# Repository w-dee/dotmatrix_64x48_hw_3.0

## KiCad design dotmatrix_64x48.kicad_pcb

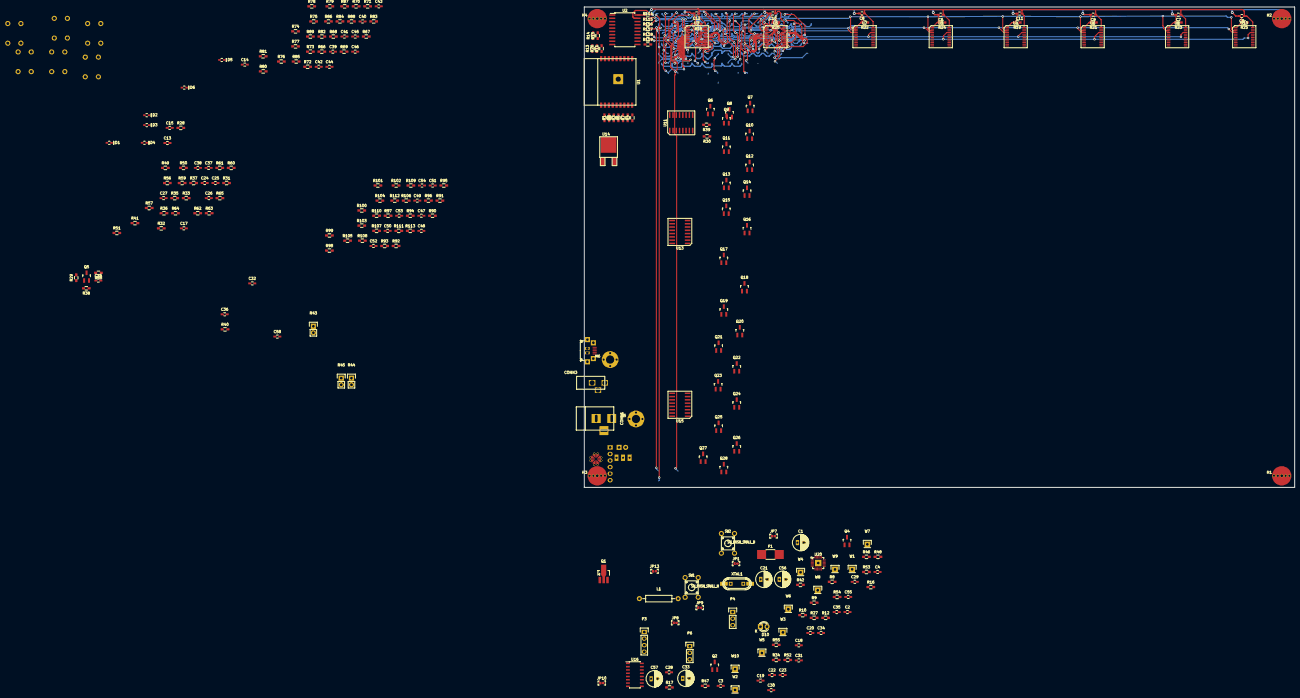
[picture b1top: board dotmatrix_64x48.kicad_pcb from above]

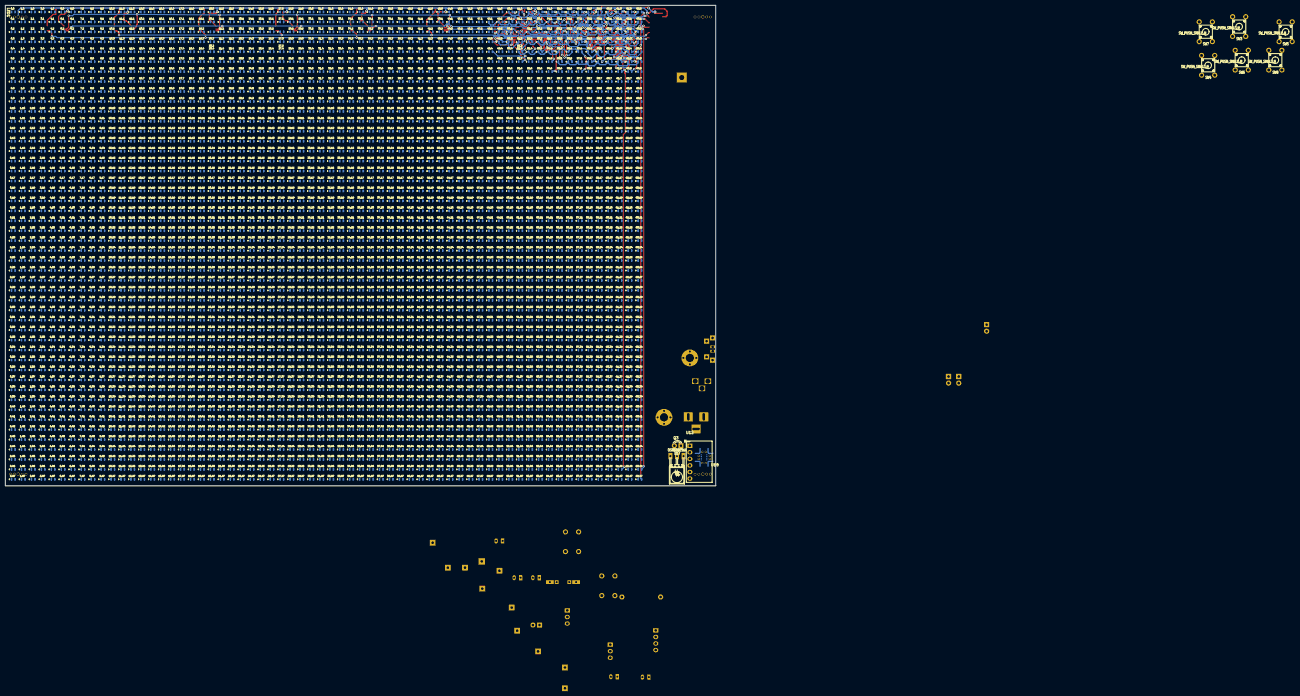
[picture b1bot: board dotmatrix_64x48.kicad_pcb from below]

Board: 2 copper layers, 275.0 x 186.0 mm, 271 parts (11 on the bottom side), 292 nets.

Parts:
C1, C21, C33, C56, C57: 100u; C_Radial_D6.3_L11.2_P2.5_hand_soldering
C2, C4, C5, C6, C7, C8, C9, C10, C11, C12, C13, C14, C15, C16, C17, C18, C19, C20, C22, C23, C24, C25, C26, C27, C28, C30, C32, C34, C35, C36, C37, C38, C39, C40, C41, C42, C43, C44, C45, C46, C47, C48, C49, C50, C51, C52, C53, C54, C55, C58: 1u; C_0603_HandSoldering
C3: 220p; C_0603_HandSoldering
C29, C31: 22p; C_0603_HandSoldering
CONN1: BARREL_JACK
CONN2: USB_OTG; ZX62R-B-5P
CONN3: BARREL_JACK; DC-JACK-3.5mm
D1, D2, D3, D4, D5, D6: D_Schottky_Small; SOD-523-mod
D10: Led_Small; LED-3MM
F1: FUSE; R_1812_HandSoldering
H1, H2, H3, H4: TEST_1P; MountingHole_stud-M3
H5, H6: TEST_1P; MountingHole_3.2mm_M3
JP1, JP7, JP8, JP9, JP10, JP13: Jumper_NC_Small; SolderJumper
L1: 2.2uH; Resistor_Horizontal_RM15mm
LED1: LED64x48; LED1608_Handsoldering_64x48
P3: CONN_01X04; Pin_Header_Straight_1x04
P4, P6: CONN_01X03; Pin_Header_Straight_1x03
Q1: Q_NPN_BCE RN5006; SOT89-3_Housing_Handsoldering
Q2, Q4: Q_NPN_BEC; SOT-23_Handsoldering
Q3: NJL7302L-F3; LED-3MM
Q5, Q6, Q7, Q8, Q9, Q10, Q11, Q12, Q13, Q14, Q15, Q16, Q17, Q18, Q19, Q20, Q21, Q22, Q23, Q24, Q25, Q26, Q27, Q28: AO3401; SOT-23_Handsoldering
R1, R2, R3, R4, R6, R7, R13, R14, R15, R17, R26, R46, R52, R114, R115, R116, R117, R118, R119: 120R; R_0603_HandSoldering
R5, R11, R18, R28, R34, R53, R54, R55: 10k; R_0603_HandSoldering
R8, R16, R27, R58, R59, R60, R61, R62, R63, R64, R65, R82, R83, R84, R85, R86, R87, R88, R89, R106, R107, R108, R109, R110, R111, R112, R113: 4.7k; R_0603_HandSoldering
R9, R10, R40: 22k; R_0603_HandSoldering
R12, R48: 1k; R_0603_HandSoldering
R19, R20, R21, R22, R23, R24, R25: R; R_0603_HandSoldering
R29, R30, R31, R32, R33, R35, R36, R37, R66, R67, R68, R69, R70, R71, R72, R73, R90, R91, R92, R93, R94, R95, R96, R97: 10R; R_0603_HandSoldering
R38, R39, R41, R49, R50, R51, R56, R57, R74, R75, R76, R77, R78, R79, R80, R81, R98, R99, R100, R101, R102, R103, R104, R105: 4.7k DNI; R_0603_HandSoldering
R42: 10k DNI; R_0603_HandSoldering
R43, R44, R45: 10k; Pin_Header_Straight_1x02
R47: 120R DNI; R_0603_HandSoldering
SW1, SW2, SW3, SW4, SW5, SW6, SW7, SW8: SW_PUSH_SMALL_H; TACT-SW-4P
U1: WROOM-02
U2: 74VHC541; SOIC-20W_7.5x12.8mm_Pitch1.27mm_W
U3, U4, U5, U6, U7, U8, U9, U10: LED1642GW; SOIC-24-0.65mm-w8.0mm
U11, U13, U15: 74HCT595; SOIC-16-1.27mm
U12: AE-BME280
U14: NJU7223; TO-252-2Lead
U16: CH340G; SOIC-16_3.9x9.9mm_Pitch1.27mm
U17: OSRB38C9AA; IRM2161_LAY
U18: BME280; BME280-handsoldering
U20: CP2104; QFN-24-1EP_4x4mm_Pitch0.5mm-handsoldering
W1, W2, W3, W4, W5, W6, W7, W8, W9, W10: TEST_1P; Pin_Header_Straight_1x01
XTAL1: 12MHz; Crystal_HC49-U_Vertical_SMD_Universal

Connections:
/row_driver/SEL1: D1.1, R90.2, U15.7
/row_driver/SEL2: D2.1, R91.2, U15.6
/row_driver/SEL3: D3.1, R92.2, U15.5
/row_driver/SEL4: D4.1, R93.2, U15.4
/row_driver/SEL5: D5.1, R94.2, U15.3
/row_driver/SEL6: D6.1, R95.2, U15.2
/row_driver/f_r0/IN0: R29.2, U11.7
/row_driver/f_r0/IN1: R30.2, U11.6
/row_driver/f_r0/IN2: R31.2, U11.5
/row_driver/f_r0/IN3: R32.2, U11.4
/row_driver/f_r0/IN4: R33.2, U11.3
/row_driver/f_r0/IN5: R35.2, U11.2
/row_driver/f_r0/IN6: R36.2, U11.1
/row_driver/f_r0/IN7: R37.2, U11.15
/row_driver/f_r8/IN0: R66.2, U13.7
/row_driver/f_r8/IN1: R67.2, U13.6
/row_driver/f_r8/IN2: R68.2, U13.5
/row_driver/f_r8/IN3: R69.2, U13.4
/row_driver/f_r8/IN4: R70.2, U13.3
/row_driver/f_r8/IN5: R71.2, U13.2
/row_driver/f_r8/IN6: R72.2, U13.1
/row_driver/f_r8/IN7: R73.2, U13.15
/row_driver/f_r16/IN6: R96.2, U15.1
/row_driver/f_r16/IN7: R97.2, U15.15
BUTTONSENSE: R13.2, R28.2, SW3.2, SW4.2, SW5.2, SW6.2, SW7.2, SW8.2, W9.1
COLCLK: R115.2, U3.3, U4.3, U5.3, U6.3, U7.3, U8.3, U9.3, U10.3, U11.11, U13.11, U15.11, W2.1
COLLATCH: R116.2, U3.4, U4.4, U5.4, U6.4, U7.4, U8.4, U9.4, U10.4, W3.1
COLPWCLK0: R117.2, U3.21, U4.21, U7.21, U8.21, W5.1
COLPWCLK1: R118.2, U5.21, U6.21, U9.21, U10.21, W10.1
COLSER: R114.2, U3.2, W1.1
COLSEROUT: U10.22, U15.14, W4.1
DC_IN: CONN1.1, F1.1, JP7.1
DTR: Q4.2, R54.2, U16.13, U20.23
ESPVDD: C18.1, C19.1, C20.1, C32.1, C33.1, C34.1, C35.1, C36.1, C55.1, C56.1, C57.1, JP8.1, L1.2, R5.2, R8.1, R9.1, R10.1, R11.2, R27.1, R40.1, R45.2, U1.1, U12.1, U17.3, U18.2, U18.6, U18.8
E_AIN: C58.1, Q3.2, R26.2, R43.1
E_COLCLK: R1.1, U2.3
E_COLLATCH: R2.1, U2.4
E_COLSER: R3.1, U2.2
E_HC595LATCH: R6.1, U2.9
E_PWCLK: R14.2, U2.6, U2.7
E_RXD: R14.1, R16.1, U1.11
E_SCL: R4.2, R9.2, R52.1, U1.8
E_SDA: R46.1, U1.14
E_TXD: R17.1, U1.12
GND: C1.2, C4.2, C5.2, C6.2, C7.2, C8.2, C9.2, C10.2, C11.2, C12.2, C13.2, C14.2, C15.2, C16.2, C17.2, C18.2, C19.2, C20.2, C21.2, C22.2, C23.2, C24.2, C25.2, C26.2, C27.2, C28.2, C29.2, C30.2, C31.2, C32.2, C33.2, C34.2, C35.2, C36.2, C37.2, C38.2, C39.2, C40.2, C41.2, C42.2, C43.2, C44.2, C45.2, C46.2, C47.2, C48.2, C49.2, C50.2, C51.2, C52.2, C53.2, C54.2, C55.2, C56.2, C57.2, C58.2, CONN1.2, CONN1.3, CONN2.5, CONN2.6, H1.1, H2.1, H3.1, H4.1, H5.1, H6.1, P3.2, P4.1, P6.1, P6.3, Q1.3, Q3.1, R18.2, R19.2, R20.2, R21.2, R22.2, R23.2, R24.2, R25.2, R34.2, R42.1, R47.1, R47.2, R48.1, R58.1, R59.1, R60.1, R61.1, R62.1, R63.1, R64.1, R65.1, R82.1, R83.1, R84.1, R85.1, R86.1, R87.1, R88.1, R89.1, R106.1, R107.1, R108.1, R109.1, R110.1, R111.1, R112.1, R113.1, SW1.2, SW2.2, U1.9, U1.13, U1.18, U2.1, U2.5, U2.8, U2.10, U2.19, U3.1, U4.1, U5.1, U6.1, U7.1, U8.1, U9.1, U10.1, U11.8, U11.13, U12.2, U13.8, U13.13, U14.3, U15.8, U15.13, U16.1, U17.2, U18.1, U18.5, U18.7, U20.2, U20.25
GPIO0_BTN: Q4.3, R4.1, SW1.1
HC595LATCH: R119.2, U11.12, U13.12, U15.12, W7.1
HC595RESET: U11.10, U13.10, U15.10, W6.1
HC595SEROUT: U11.9, W8.1
IR_IN: R15.2, R40.2, U17.1
IR_OUT: C2.2, D10.2, R7.1
LEDLOGICVDD: C5.1, C6.1, C7.1, C8.1, C9.1, C10.1, C11.1, C12.1, JP13.2, L1.1, P6.2, R28.1, U2.20, U3.24, U4.24, U5.24, U6.24, U7.24, U8.24, U9.24, U10.24
LEDVDD: C13.1, C14.1, C15.1, C16.1, C17.1, C24.1, C25.1, C26.1, C27.1, C37.1, C38.1, C39.1, C40.1, C41.1, C42.1, C43.1, C44.1, C45.1, C46.1, C47.1, C48.1, C49.1, C50.1, C51.1, C52.1, C53.1, C54.1, JP1.2, Q5.2, Q6.2, Q7.2, Q8.2, Q9.2, Q10.2, Q11.2, Q12.2, Q13.2, Q14.2, Q15.2, Q16.2, Q17.2, Q18.2, Q19.2, Q20.2, Q21.2, Q22.2, Q23.2, Q24.2, Q25.2, Q26.2, Q27.2, Q28.2, R38.1, R39.1, R41.1, R49.1, R50.1, R51.1, R56.1, R57.1, R74.1, R75.1, R76.1, R77.1, R78.1, R79.1, R80.1, R81.1, R98.1, R99.1, R100.1, R101.1, R102.1, R103.1, R104.1, R105.1, U11.16, U13.16, U15.16
unnamed: C1.1, C23.1, JP13.1, U14.1
unnamed: C2.1, C3.2, R12.1
unnamed: C3.1, Q1.1, R12.2, R42.2
unnamed: C28.1, C30.1, JP8.2, R53.1, U16.4, U16.16, U20.5, U20.6, U20.7
unnamed: C29.1, U16.7, XTAL1.1
unnamed: C31.1, U16.8, XTAL1.2
unnamed: CONN2.1, JP7.2
unnamed: CONN3.2, CONN3.3, Q1.2
unnamed: D1.2, SW3.1
unnamed: D2.2, SW4.1
unnamed: D3.2, SW5.1
unnamed: D4.2, SW6.1
unnamed: D5.2, SW7.1
unnamed: D6.2, SW8.1
unnamed: D10.1, R48.2
unnamed: JP9.1, U16.2, U20.21
unnamed: JP10.1, U16.3, U20.20
unnamed: Q2.1, R54.1
unnamed: Q4.1, R55.1
unnamed: Q5.1, R29.1, R38.2
unnamed: Q6.1, R30.1, R39.2
unnamed: Q7.1, R31.1, R41.2
unnamed: Q8.1, R32.1, R49.2
unnamed: Q9.1, R33.1, R50.2
unnamed: Q10.1, R35.1, R51.2
unnamed: Q11.1, R36.1, R56.2
unnamed: Q12.1, R37.1, R57.2
unnamed: Q13.1, R66.1, R74.2
unnamed: Q14.1, R67.1, R75.2
unnamed: Q15.1, R68.1, R76.2
unnamed: Q16.1, R69.1, R77.2
unnamed: Q17.1, R70.1, R78.2
unnamed: Q18.1, R71.1, R79.2
unnamed: Q19.1, R72.1, R80.2
unnamed: Q20.1, R73.1, R81.2
unnamed: Q21.1, R90.1, R98.2
unnamed: Q22.1, R91.1, R99.2
unnamed: Q23.1, R92.1, R100.2
unnamed: Q24.1, R93.1, R101.2
unnamed: Q25.1, R94.1, R102.2
unnamed: Q26.1, R95.1, R103.2
unnamed: Q27.1, R96.1, R104.2
unnamed: Q28.1, R97.1, R105.2
unnamed: R1.2, U1.3
unnamed: R2.2, U1.4
unnamed: R3.2, U1.5
unnamed: R5.1, U1.2
unnamed: R7.2, R10.2, U1.7
unnamed: R13.1, U1.17
unnamed: R15.1, U1.10
unnamed: R18.1, U3.23
unnamed: R19.1, U4.23
unnamed: R20.1, U5.23
unnamed: R21.1, U6.23
unnamed: R22.1, U7.23
unnamed: R23.1, U8.23
unnamed: R24.1, U9.23
unnamed: R25.1, U10.23
unnamed: R26.1, U1.16
unnamed: R6.2, R34.1, U1.6
unnamed: R43.2, R44.1
unnamed: R44.2, R45.1
unnamed: R53.2, U20.9
unnamed: R114.1, U2.18
unnamed: R115.1, U2.17
unnamed: R116.1, U2.16
unnamed: R117.1, U2.14
unnamed: R118.1, U2.13
unnamed: R119.1, U2.11
unnamed: U3.22, U5.2
unnamed: U4.2, U9.22
unnamed: U4.22, U6.2
unnamed: U5.22, U7.2
unnamed: U6.22, U8.2
unnamed: U7.22, U9.2
unnamed: U8.22, U10.2
unnamed: U11.14, U13.9
unnamed: U13.14, U15.9
RST: Q2.3, R11.1, SW2.1, U1.15
RTS: Q2.2, R55.2, U16.14, U20.19
RXD: JP9.2, P3.3, R16.2
SCL: P4.2, R8.2, R52.2, U12.6, U18.4
SDA: P4.3, R27.2, R46.2, U12.4, U18.3
TXD: JP10.2, P3.4, R17.2
USB_D_N: CONN2.2, U16.6, U20.4
USB_D_P: CONN2.3, U16.5, U20.3
VCC: C4.1, C21.1, C22.1, CONN3.1, F1.2, JP1.1, U14.2, U20.8
ce0: LED1.1, U10.20
ce1: LED1.2, U10.18
ce2: LED1.3, U10.16
ce3: LED1.4, U10.14
ce4: LED1.5, U10.12
ce5: LED1.6, U10.10
ce6: LED1.7, U10.8
ce7: LED1.8, U10.6
ce8: LED1.9, U8.20
ce9: LED1.10, U8.18
ce10: LED1.11, U8.16
ce11: LED1.12, U8.14
ce12: LED1.13, U8.12
ce13: LED1.14, U8.10
ce14: LED1.15, U8.8
ce15: LED1.16, U8.6
ce16: LED1.17, U6.20
ce17: LED1.18, U6.18
ce18: LED1.19, U6.16
ce19: LED1.20, U6.14
ce20: LED1.21, U6.12
ce21: LED1.22, U6.10
ce22: LED1.23, U6.8
ce23: LED1.24, U6.6
ce24: LED1.25, U4.20
ce25: LED1.26, U4.18
ce26: LED1.27, U4.16
ce27: LED1.28, U4.14
ce28: LED1.29, U4.12
ce29: LED1.30, U4.10
ce30: LED1.31, U4.8
ce31: LED1.32, U4.6
ce32: LED1.33, U9.20
ce33: LED1.34, U9.18
ce34: LED1.35, U9.16
ce35: LED1.36, U9.14
ce36: LED1.37, U9.12
ce37: LED1.38, U9.10
ce38: LED1.39, U9.8
ce39: LED1.40, U9.6
ce40: LED1.41, U7.20
ce41: LED1.42, U7.18
ce42: LED1.43, U7.16
ce43: LED1.44, U7.14
ce44: LED1.45, U7.12
ce45: LED1.46, U7.10
ce46: LED1.47, U7.8
ce47: LED1.48, U7.6
ce48: LED1.49, U5.20
ce49: LED1.50, U5.18
ce50: LED1.51, U5.16
ce51: LED1.52, U5.14
ce52: LED1.53, U5.12
ce53: LED1.54, U5.10
ce54: LED1.55, U5.8
ce55: LED1.56, U5.6
ce56: LED1.57, U3.20
ce57: LED1.58, U3.18
ce58: LED1.59, U3.16
ce59: LED1.60, U3.14
ce60: LED1.61, U3.12
ce61: LED1.62, U3.10
ce62: LED1.63, U3.8
ce63: LED1.64, U3.6
co0: LED1.65, U10.19
co1: LED1.66, U10.17
co2: LED1.67, U10.15
co3: LED1.68, U10.13
co4: LED1.69, U10.11
co5: LED1.70, U10.9
co6: LED1.71, U10.7
co7: LED1.72, U10.5
co8: LED1.73, U8.19
co9: LED1.74, U8.17
co10: LED1.75, U8.15
co11: LED1.76, U8.13
co12: LED1.77, U8.11
co13: LED1.78, U8.9
co14: LED1.79, U8.7
co15: LED1.80, U8.5
co16: LED1.81, U6.19
co17: LED1.82, U6.17
co18: LED1.83, U6.15
co19: LED1.84, U6.13
co20: LED1.85, U6.11
co21: LED1.86, U6.9
co22: LED1.87, U6.7
co23: LED1.88, U6.5
co24: LED1.89, U4.19
co25: LED1.90, U4.17
co26: LED1.91, U4.15
co27: LED1.92, U4.13
co28: LED1.93, U4.11
co29: LED1.94, U4.9
co30: LED1.95, U4.7
co31: LED1.96, U4.5
co32: LED1.97, U9.19
co33: LED1.98, U9.17
co34: LED1.99, U9.15
co35: LED1.100, U9.13
co36: LED1.101, U9.11
co37: LED1.102, U9.9
co38: LED1.103, U9.7
co39: LED1.104, U9.5
co40: LED1.105, U7.19
co41: LED1.106, U7.17
co42: LED1.107, U7.15
co43: LED1.108, U7.13
co44: LED1.109, U7.11
co45: LED1.110, U7.9
co46: LED1.111, U7.7
co47: LED1.112, U7.5
co48: LED1.113, U5.19
co49: LED1.114, U5.17
co50: LED1.115, U5.15
co51: LED1.116, U5.13
co52: LED1.117, U5.11
co53: LED1.118, U5.9
co54: LED1.119, U5.7
co55: LED1.120, U5.5
co56: LED1.121, U3.19
co57: LED1.122, U3.17
co58: LED1.123, U3.15
co59: LED1.124, U3.13
co60: LED1.125, U3.11
co61: LED1.126, U3.9
co62: LED1.127, U3.7
co63: LED1.128, U3.5
r0: LED1.201, Q5.3, R58.2
r1: LED1.202, Q6.3, R59.2
r2: LED1.203, Q7.3, R60.2
r3: LED1.204, Q8.3, R61.2
r4: LED1.205, Q9.3, R62.2
r5: LED1.206, Q10.3, R63.2
r6: LED1.207, Q11.3, R64.2
r7: LED1.208, Q12.3, R65.2
r8: LED1.209, Q13.3, R82.2
r9: LED1.210, Q14.3, R83.2
r10: LED1.211, Q15.3, R84.2
r11: LED1.212, Q16.3, R85.2
r12: LED1.213, Q17.3, R86.2
r13: LED1.214, Q18.3, R87.2
r14: LED1.215, Q19.3, R88.2
r15: LED1.216, Q20.3, R89.2
r16: LED1.217, Q21.3, R106.2
r17: LED1.218, Q22.3, R107.2
r18: LED1.219, Q23.3, R108.2
r19: LED1.220, Q24.3, R109.2
r20: LED1.221, Q25.3, R110.2
r21: LED1.222, Q26.3, R111.2
r22: LED1.223, Q27.3, R112.2
r23: LED1.224, Q28.3, R113.2

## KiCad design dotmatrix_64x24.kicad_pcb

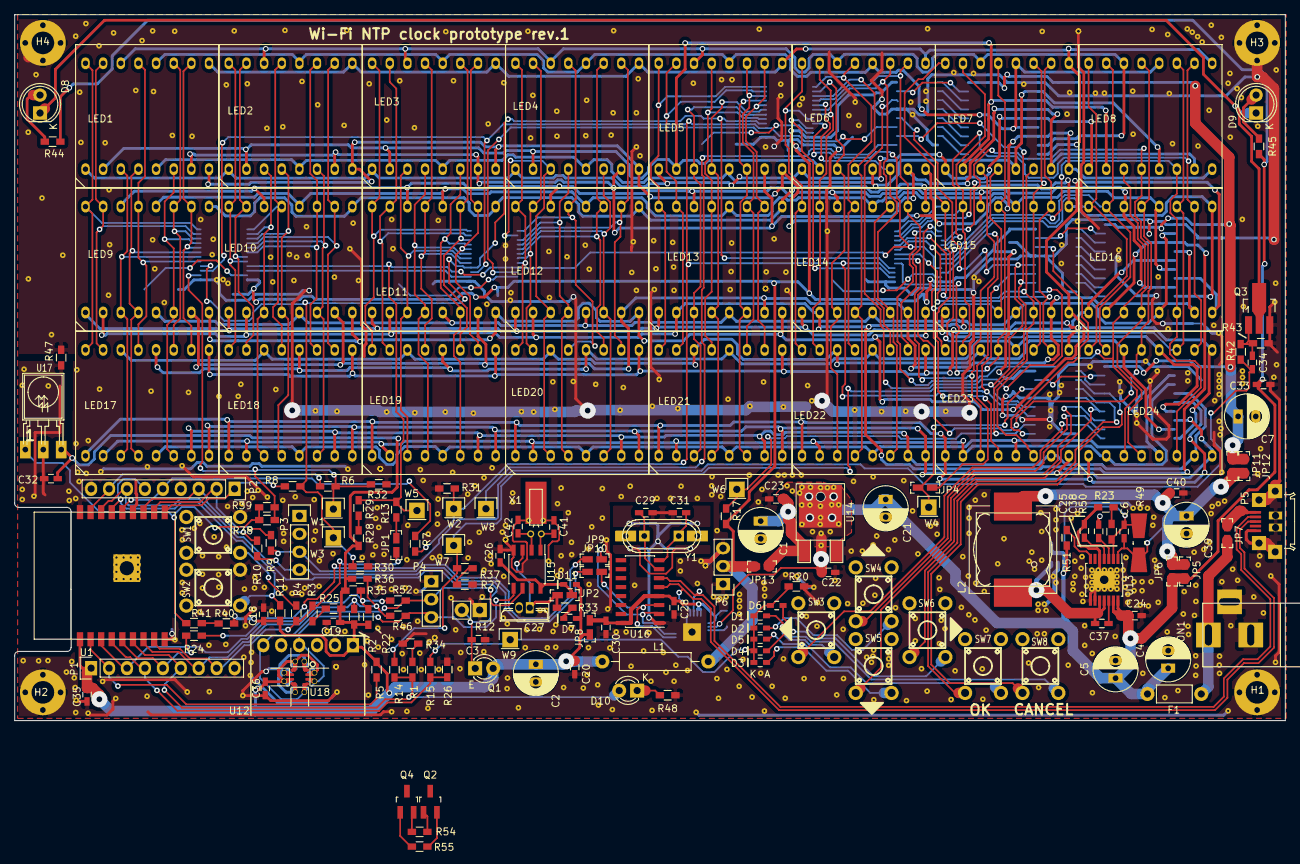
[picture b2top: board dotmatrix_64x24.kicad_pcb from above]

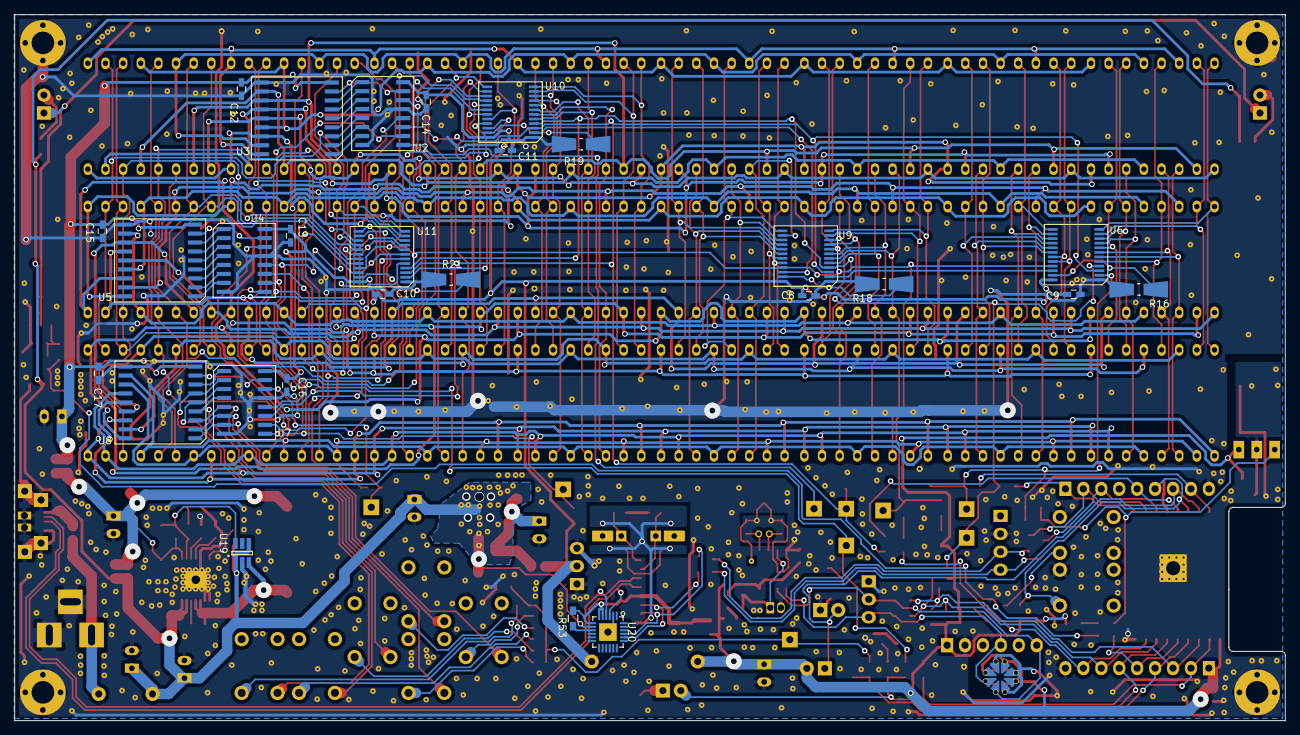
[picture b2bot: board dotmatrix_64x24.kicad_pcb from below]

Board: 2 copper layers, 180.0 x 100.0 mm, 201 parts (27 on the bottom side), 202 nets.

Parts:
C1, C2, C4, C5, C7, C21, C39: 100u; C_Radial_D6.3_L11.2_P2.5_hand_soldering
C3, C8, C9, C10, C11, C12, C13, C14, C15, C16, C17, C18, C19, C20, C22, C23, C24, C25, C26, C28, C30, C32, C33, C35, C36, C37, C38, C40: 1u; C_0603_HandSoldering
C6, C29, C31, C41, C42: 22p; C_0603_HandSoldering
C27: 0.22F; DCK_614
C34: 220p; C_0603_HandSoldering
CON1: BARREL_JACK
D1, D2, D3, D4, D5, D6, D7, D11: D_Schottky_Small; SOD-523-mod
D8, D9: Led_Small; LED-5MM
D10: Led_Small; LED-3MM
F1: FUSE; Resistor_Horizontal_RM7mm
H1, H2, H3, H4: TEST_1P; MountingHole_3.2mm_M3
JP1, JP2, JP4, JP5, JP6, JP7, JP8, JP9, JP10, JP11, JP12, JP13: Jumper_NC_Small; SolderJumper
L1: 100uH; Resistor_Horizontal_RM15mm
L2: 4.9uH; Choke_SMD_12x12mm_10.4x10.4mm_compat_h4.5mm_handsoldering
LED1, LED2, LED3, LED4, LED5, LED6, LED7, LED8, LED9, LED10, LED11, LED12, LED13, LED14, LED15, LED16, LED17, LED18, LED19, LED20, LED21, LED22, LED23, LED24: LED8x8; LED8x8,0.8x0.8inch
P1, P2: CONN_01X09; Pin_Header_Straight_1x09
P3: CONN_01X04; Pin_Header_Straight_1x04
P4, P6: CONN_01X03; Pin_Header_Straight_1x03
P5: USB_OTG; ZX62R-B-5P
Q1: NJL7302L-F3; LED-3MM
Q2, Q4: Q_NPN_BEC; SOT-23_Handsoldering
Q3: Q_NPN_BCE RN5006; SOT89-3_Housing_Handsoldering
R1, R2, R3, R5, R11, R17, R20, R22, R23, R25, R26, R27, R28, R29, R30, R31, R34, R35, R36, R37, R38, R39, R40, R41, R50, R51, R53, R54, R55: 10k; R_0603_HandSoldering
R4, R42, R48: 1k; R_0603_HandSoldering
R6, R7, R8, R9, R10, R13, R14, R15, R24, R33, R46, R52: 120R; R_0603_HandSoldering
R12: 50k; Pin_Header_Straight_1x02
R16, R18, R19, R21, R49: R; Resistor_SMDuniversal_0805to1206_HandSoldering
R32, R43: 10k DNI; R_0603_HandSoldering
R44, R45: 10R; R_0603_HandSoldering
R47: 120R DNI; R_0603_HandSoldering
SW1, SW2, SW3, SW4, SW5, SW6, SW7, SW8: SW_PUSH_SMALL_H; TACT-SW-4P
U1: WROOM-02
U2, U4, U7: 74HC595-alt-vdd; SOIC-16-1.27mm-w7.8mm
U3, U5, U8: TD62783; SOIC-18-1.27mm-w11.9mm
U6, U9, U10, U11: LED1642GW; SOIC-24-0.65mm-w8.0mm
U12: AE-BME280
U13: TPS54426; TSSOP-14-EP-hole_4.4x5mm_Pitch0.65mm
U14: NJU7223; TO-252-2Lead
U15: DS1307; SOIC-8_3.9x4.9mm_Pitch1.27mm
U16: CH340G; SOIC-16_3.9x9.9mm_Pitch1.27mm
U17: OSRB38C9AA; IRM2161_LAY
U18: BME280; BME280-handsoldering
U19: AP3419; SOT-23-6_Handsoldering
U20: CP2104; QFN-24-1EP_4x4mm_Pitch0.5mm-handsoldering
W1, W2, W3, W4, W5, W6, W7, W8, W9: TEST_1P; Pin_Header_Straight_1x01
X1: CRYSTAL_SMD; Crystal_Round_Horizontal_2mm_SHIELD
Y1: 12MHz; Crystal_HC49-U_Vertical_SMD_Universal

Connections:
/DC_IN: CON1.1, F1.1, JP7.1
/DTR: Q4.2, R54.2, U16.13, U20.23
/ESPVDD: C2.1, C18.1, C19.1, C20.1, C32.1, C35.1, C36.1, D7.2, D11.2, JP8.1, L1.2, P1.1, Q1.2, R2.1, R5.1, R11.1, R22.1, R25.1, R28.1, R35.1, R36.1, R40.1, U1.1, U12.1, U17.3, U18.2, U18.6, U18.8
/GPIO0_BTN: Q4.3, R4.1, SW1.1
/IR_IN: R38.1, R39.1, R41.2, U17.1
/IR_OUT: C34.2, R24.1, R42.1
/IR_Sensor_RTC/IR_LED_DRIVE: D8.1, D9.1, Q3.2
/LEDLOGICVDD: C8.1, C9.1, C10.1, C11.1, C13.1, C14.1, C16.1, JP13.2, L1.1, P6.2, R17.1, U2.16, U4.16, U6.24, U7.16, U9.24, U10.24, U11.24
/RST: P2.6, Q2.3, R11.2, SW2.1, U1.15
/RTS: Q2.2, R55.2, U16.14, U20.19
/RXD: JP9.2, P3.3, R9.2
/SCL: P4.2, R52.2, U12.6, U15.6, U18.4
/SDA: P4.3, R46.2, U12.4, U15.5, U18.3
/Sheet57A04605/BUTTONSENSE: D1.1, D2.1, D3.1, D4.1, D5.1, D6.1, R15.2, R20.1, W9.1
/Sheet57A04605/COLCLK: R7.2, R31.1, U2.11, U4.11, U6.3, U7.11, U9.3, U10.3, U11.3, W2.1
/Sheet57A04605/COLLATCH: R8.2, R30.1, U6.4, U9.4, U10.4, U11.4, W3.1
/Sheet57A04605/COLPWCLK: R13.2, R29.2, U6.21, U9.21, U10.21, U11.21, W5.1
/Sheet57A04605/COLSER: R6.2, R32.1, R38.2, R39.2, U6.2, W1.1
/Sheet57A04605/COLSEROUT: JP4.2, U11.22
/Sheet57A04605/HC595LATCH: R14.2, R37.1, U2.12, U4.12, U7.12, W7.1
/Sheet57A04605/HC595RESET: R17.2, U2.10, U4.10, U7.10, W6.1
/Sheet57A04605/HC595SER: JP4.1, U7.14, W4.1
/Sheet57A04605/HC595SEROUT: U2.9, W8.1
/Sheet57A04605/LEDREG_FB: C6.2, R49.2, R50.1, U13.2, U19.6
/Sheet57A04605/LEDREG_LX: C37.1, L2.1, U13.10, U13.11, U19.3
/Sheet57A04605/LEDVDD: C7.1, C12.1, C15.1, C17.1, JP11.2, JP12.2, U3.9, U5.9, U8.9
/Sheet57A04605/SEL1: SW3.1, U7.7, U8.1
/Sheet57A04605/SEL2: SW4.1, U7.6, U8.2
/Sheet57A04605/SEL3: SW5.1, U7.5, U8.3
/Sheet57A04605/SEL4: SW6.1, U7.4, U8.4
/Sheet57A04605/SEL5: SW7.1, U7.3, U8.5
/Sheet57A04605/SEL6: SW8.1, U7.2, U8.6
/Sheet57A04605/c1: LED1.13, LED9.13, LED17.13, U6.5
/Sheet57A04605/c2: LED1.3, LED9.3, LED17.3, U6.6
/Sheet57A04605/c3: LED1.4, LED9.4, LED17.4, U6.7
/Sheet57A04605/c4: LED1.10, LED9.10, LED17.10, U6.8
/Sheet57A04605/c5: LED1.6, LED9.6, LED17.6, U6.9
/Sheet57A04605/c6: LED1.11, LED9.11, LED17.11, U6.10
/Sheet57A04605/c7: LED1.15, LED9.15, LED17.15, U6.11
/Sheet57A04605/c8: LED1.16, LED9.16, LED17.16, U6.12
/Sheet57A04605/c9: LED2.13, LED10.13, LED18.13, U6.13
/Sheet57A04605/c10: LED2.3, LED10.3, LED18.3, U6.14
/Sheet57A04605/c11: LED2.4, LED10.4, LED18.4, U6.15
/Sheet57A04605/c12: LED2.10, LED10.10, LED18.10, U6.16
/Sheet57A04605/c13: LED2.6, LED10.6, LED18.6, U6.17
/Sheet57A04605/c14: LED2.11, LED10.11, LED18.11, U6.18
/Sheet57A04605/c15: LED2.15, LED10.15, LED18.15, U6.19
/Sheet57A04605/c16: LED2.16, LED10.16, LED18.16, U6.20
/Sheet57A04605/c17: LED3.13, LED11.13, LED19.13, U9.5
/Sheet57A04605/c18: LED3.3, LED11.3, LED19.3, U9.6
/Sheet57A04605/c19: LED3.4, LED11.4, LED19.4, U9.7
/Sheet57A04605/c20: LED3.10, LED11.10, LED19.10, U9.8
/Sheet57A04605/c21: LED3.6, LED11.6, LED19.6, U9.9
/Sheet57A04605/c22: LED3.11, LED11.11, LED19.11, U9.10
/Sheet57A04605/c23: LED3.15, LED11.15, LED19.15, U9.11
/Sheet57A04605/c24: LED3.16, LED11.16, LED19.16, U9.12
/Sheet57A04605/c25: LED4.13, LED12.13, LED20.13, U9.13
/Sheet57A04605/c26: LED4.3, LED12.3, LED20.3, U9.14
/Sheet57A04605/c27: LED4.4, LED12.4, LED20.4, U9.15
/Sheet57A04605/c28: LED4.10, LED12.10, LED20.10, U9.16
/Sheet57A04605/c29: LED4.6, LED12.6, LED20.6, U9.17
/Sheet57A04605/c30: LED4.11, LED12.11, LED20.11, U9.18
/Sheet57A04605/c31: LED4.15, LED12.15, LED20.15, U9.19
/Sheet57A04605/c32: LED4.16, LED12.16, LED20.16, U9.20
/Sheet57A04605/c33: LED5.13, LED13.13, LED21.13, U10.5
/Sheet57A04605/c34: LED5.3, LED13.3, LED21.3, U10.6
/Sheet57A04605/c35: LED5.4, LED13.4, LED21.4, U10.7
/Sheet57A04605/c36: LED5.10, LED13.10, LED21.10, U10.8
/Sheet57A04605/c37: LED5.6, LED13.6, LED21.6, U10.9
/Sheet57A04605/c38: LED5.11, LED13.11, LED21.11, U10.10
/Sheet57A04605/c39: LED5.15, LED13.15, LED21.15, U10.11
/Sheet57A04605/c40: LED5.16, LED13.16, LED21.16, U10.12
/Sheet57A04605/c41: LED6.13, LED14.13, LED22.13, U10.13
/Sheet57A04605/c42: LED6.3, LED14.3, LED22.3, U10.14
/Sheet57A04605/c43: LED6.4, LED14.4, LED22.4, U10.15
/Sheet57A04605/c44: LED6.10, LED14.10, LED22.10, U10.16
/Sheet57A04605/c45: LED6.6, LED14.6, LED22.6, U10.17
/Sheet57A04605/c46: LED6.11, LED14.11, LED22.11, U10.18
/Sheet57A04605/c47: LED6.15, LED14.15, LED22.15, U10.19
/Sheet57A04605/c48: LED6.16, LED14.16, LED22.16, U10.20
/Sheet57A04605/c49: LED7.13, LED15.13, LED23.13, U11.5
/Sheet57A04605/c50: LED7.3, LED15.3, LED23.3, U11.6
/Sheet57A04605/c51: LED7.4, LED15.4, LED23.4, U11.7
/Sheet57A04605/c52: LED7.10, LED15.10, LED23.10, U11.8
/Sheet57A04605/c53: LED7.6, LED15.6, LED23.6, U11.9
/Sheet57A04605/c54: LED7.11, LED15.11, LED23.11, U11.10
/Sheet57A04605/c55: LED7.15, LED15.15, LED23.15, U11.11
/Sheet57A04605/c56: LED7.16, LED15.16, LED23.16, U11.12
/Sheet57A04605/c57: LED8.13, LED16.13, LED24.13, U11.13
/Sheet57A04605/c58: LED8.3, LED16.3, LED24.3, U11.14
/Sheet57A04605/c59: LED8.4, LED16.4, LED24.4, U11.15
/Sheet57A04605/c60: LED8.10, LED16.10, LED24.10, U11.16
/Sheet57A04605/c61: LED8.6, LED16.6, LED24.6, U11.17
/Sheet57A04605/c62: LED8.11, LED16.11, LED24.11, U11.18
/Sheet57A04605/c63: LED8.15, LED16.15, LED24.15, U11.19
/Sheet57A04605/c64: LED8.16, LED16.16, LED24.16, U11.20
/Sheet57A04605/r1: LED1.9, LED2.9, LED3.9, LED4.9, LED5.9, LED6.9, LED7.9, LED8.9, U3.18
/Sheet57A04605/r2: LED1.14, LED2.14, LED3.14, LED4.14, LED5.14, LED6.14, LED7.14, LED8.14, U3.17
/Sheet57A04605/r3: LED1.8, LED2.8, LED3.8, LED4.8, LED5.8, LED6.8, LED7.8, LED8.8, U3.16
/Sheet57A04605/r4: LED1.12, LED2.12, LED3.12, LED4.12, LED5.12, LED6.12, LED7.12, LED8.12, U3.15
/Sheet57A04605/r5: LED1.1, LED2.1, LED3.1, LED4.1, LED5.1, LED6.1, LED7.1, LED8.1, U3.14
/Sheet57A04605/r6: LED1.7, LED2.7, LED3.7, LED4.7, LED5.7, LED6.7, LED7.7, LED8.7, U3.13
/Sheet57A04605/r7: LED1.2, LED2.2, LED3.2, LED4.2, LED5.2, LED6.2, LED7.2, LED8.2, U3.12
/Sheet57A04605/r8: LED1.5, LED2.5, LED3.5, LED4.5, LED5.5, LED6.5, LED7.5, LED8.5, U3.11
/Sheet57A04605/r9: LED9.9, LED10.9, LED11.9, LED12.9, LED13.9, LED14.9, LED15.9, LED16.9, U5.18
/Sheet57A04605/r10: LED9.14, LED10.14, LED11.14, LED12.14, LED13.14, LED14.14, LED15.14, LED16.14, U5.17
/Sheet57A04605/r11: LED9.8, LED10.8, LED11.8, LED12.8, LED13.8, LED14.8, LED15.8, LED16.8, U5.16
/Sheet57A04605/r12: LED9.12, LED10.12, LED11.12, LED12.12, LED13.12, LED14.12, LED15.12, LED16.12, U5.15
/Sheet57A04605/r13: LED9.1, LED10.1, LED11.1, LED12.1, LED13.1, LED14.1, LED15.1, LED16.1, U5.14
/Sheet57A04605/r14: LED9.7, LED10.7, LED11.7, LED12.7, LED13.7, LED14.7, LED15.7, LED16.7, U5.13
/Sheet57A04605/r15: LED9.2, LED10.2, LED11.2, LED12.2, LED13.2, LED14.2, LED15.2, LED16.2, U5.12
/Sheet57A04605/r16: LED9.5, LED10.5, LED11.5, LED12.5, LED13.5, LED14.5, LED15.5, LED16.5, U5.11
/Sheet57A04605/r17: LED17.9, LED18.9, LED19.9, LED20.9, LED21.9, LED22.9, LED23.9, LED24.9, U8.18
/Sheet57A04605/r18: LED17.14, LED18.14, LED19.14, LED20.14, LED21.14, LED22.14, LED23.14, LED24.14, U8.17
/Sheet57A04605/r19: LED17.8, LED18.8, LED19.8, LED20.8, LED21.8, LED22.8, LED23.8, LED24.8, U8.16
/Sheet57A04605/r20: LED17.12, LED18.12, LED19.12, LED20.12, LED21.12, LED22.12, LED23.12, LED24.12, U8.15
/Sheet57A04605/r21: LED17.1, LED18.1, LED19.1, LED20.1, LED21.1, LED22.1, LED23.1, LED24.1, U8.14
/Sheet57A04605/r22: LED17.7, LED18.7, LED19.7, LED20.7, LED21.7, LED22.7, LED23.7, LED24.7, U8.13
/Sheet57A04605/r23: LED17.2, LED18.2, LED19.2, LED20.2, LED21.2, LED22.2, LED23.2, LED24.2, U8.12
/Sheet57A04605/r24: LED17.5, LED18.5, LED19.5, LED20.5, LED21.5, LED22.5, LED23.5, LED24.5, U8.11
/TXD: JP10.2, P3.4, R10.2
/USB_D_N: P5.2, U16.6, U20.4
/USB_D_P: P5.3, U16.5, U20.3
GND: C1.2, C2.2, C3.2, C4.2, C5.2, C7.2, C8.2, C9.2, C10.2, C11.2, C12.2, C13.2, C14.2, C15.2, C16.2, C17.2, C18.2, C19.2, C20.2, C21.2, C22.2, C23.2, C24.2, C25.2, C26.2, C27.2, C28.2, C29.2, C30.2, C31.2, C32.2, C33.2, C35.2, C36.2, C38.2, C39.2, C40.2, C41.2, C42.2, CON1.2, CON1.3, H1.1, H2.1, H3.1, H4.1, P1.9, P2.4, P2.9, P3.2, P4.1, P5.5, P5.6, P6.1, P6.3, Q3.3, R12.1, R16.2, R18.2, R19.2, R20.2, R21.2, R23.2, R26.2, R27.2, R30.2, R31.2, R32.2, R34.1, R43.1, R47.1, R47.2, R48.1, SW1.2, SW2.2, U1.9, U1.13, U1.18, U2.8, U2.13, U3.10, U4.8, U4.13, U5.10, U6.1, U7.8, U7.13, U8.10, U9.1, U10.1, U11.1, U12.2, U13.5, U13.8, U13.9, U13.15, U14.3, U15.4, U16.1, U17.2, U18.1, U18.5, U18.7, U19.2, U20.2, U20.25, X1.3
unnamed: C1.1, C23.1, JP13.1, U14.1
unnamed: C3.1, P2.7, Q1.1, R12.2, U1.16
unnamed: C25.1, U13.4
unnamed: C26.1, D11.1, JP2.1, U15.8
unnamed: C27.1, JP2.2, R33.1, U15.3
unnamed: C28.1, C30.1, JP8.2, R53.1, U16.4, U16.16, U20.5, U20.6, U20.7
unnamed: C29.1, U16.7, Y1.1
unnamed: C31.1, U16.8, Y1.2
unnamed: C34.1, Q3.1, R42.2, R43.2
unnamed: C37.2, U13.12
unnamed: C38.1, U13.3
unnamed: C6.1, C39.1, C40.1, JP5.2, JP6.2, JP11.1, JP12.1, L2.2, R49.1, U13.1
unnamed: C41.1, U15.1, X1.2
unnamed: C42.1, U15.2, X1.1
unnamed: D1.2, SW3.2
unnamed: D2.2, SW4.2
unnamed: D3.2, SW5.2
unnamed: D4.2, SW6.2
unnamed: D5.2, SW7.2
unnamed: D6.2, SW8.2
unnamed: D7.1, R33.2
unnamed: D8.2, R44.1
unnamed: D9.2, R45.1
unnamed: D10.1, R48.2
unnamed: D10.2, P1.6, R1.2, R14.1, U1.6
unnamed: JP1.1, P1.8, R3.2, R4.2, U1.8
unnamed: JP1.2, R13.1
unnamed: JP7.2, P5.1
unnamed: JP9.1, U16.2, U20.21
unnamed: JP10.1, U16.3, U20.20
unnamed: P1.2, R5.2, U1.2
unnamed: P1.3, R22.2, R35.2, R52.1, U1.3
unnamed: P1.4, R15.1, R26.1, U1.4
unnamed: P1.5, R24.2, U1.5
unnamed: P1.7, R2.2, R36.2, R46.1, U1.7
unnamed: P2.1, R8.1, U1.10
unnamed: P2.2, R9.1, U1.11
unnamed: P2.3, R10.1, U1.12
unnamed: P2.5, R7.1, U1.14
unnamed: P2.8, R6.1, U1.17
unnamed: Q2.1, R54.1
unnamed: Q4.1, R55.1
unnamed: R1.1, R34.2
unnamed: R16.1, U6.23
unnamed: R18.1, U9.23
unnamed: R19.1, U10.23
unnamed: R21.1, U11.23
unnamed: R23.1, R50.2
unnamed: R3.1, R25.2
unnamed: R27.1, R37.2
unnamed: R28.2, R29.1
unnamed: R40.2, R41.1
unnamed: R51.2, U13.7
unnamed: R53.2, U20.9
unnamed: U2.1, U3.7
unnamed: U2.2, U3.6
unnamed: U2.3, U3.5
unnamed: U2.4, U3.4
unnamed: U2.5, U3.3
unnamed: U2.6, U3.2
unnamed: U2.7, U3.1
unnamed: U2.14, U4.9
unnamed: U2.15, U3.8
unnamed: U4.1, U5.7
unnamed: U4.2, U5.6
unnamed: U4.3, U5.5
unnamed: U4.4, U5.4
unnamed: U4.5, U5.3
unnamed: U4.6, U5.2
unnamed: U4.7, U5.1
unnamed: U4.14, U7.9
unnamed: U4.15, U5.8
unnamed: U6.22, U9.2
unnamed: U7.1, U8.7
unnamed: U7.15, U8.8
unnamed: U9.22, U10.2
unnamed: U10.22, U11.2
VCC: C4.1, C5.1, C21.1, C22.1, C24.1, C33.1, F1.2, JP5.1, JP6.1, R44.2, R45.2, R51.1, U13.13, U13.14, U14.2, U19.1, U19.4, U20.8

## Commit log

2016-08-12 Added DCDC converter to get low power dissipation in LED driver IC
2016-08-16 Added mounting holes, DS1207+ RTC, and more
2016-08-18 Added CH340G USB-to-Serial chip
2016-08-19 filled copper zones, placed via stitching ... etc.
2016-08-20 Ground plane fix, XTAL footprint fix
2016-08-20 Added IR remote control functionality
2016-08-21 Fixed electrolyric capacitor diameter
2016-08-23 Separated sensors/IR/RTC schematic sheet and improved IR transistor drive circuit
2016-08-23 Added BME280 hand-soldering pattern
2016-08-23 Adjusted Via diameter
2016-08-24 Various fixes
2016-08-25 Various fix and improvements
2016-08-25 Fixed current flow, cut antenna area of the PCB
2016-08-26 Various fixes, notably removing front coppor pour under Murata DC-DC converter
2016-08-31 To use TSP54426 instead of Murata OKL
2016-09-01 Trace fixes etc.
2016-09-02 WROOM-02 EP thermal fix
2016-09-02 Trace fixes
2016-09-05 To use COLSER signal as both IR input and column data signal output
2016-09-08 Improved crystal stability by adding local ground plane
2016-09-09 Modified to improve impedance of the reference voltage of LED Driver's current setting R
2016-09-10 Track cleanup
2016-09-11 Improved hand-solderbility and fixed traces
2016-09-12 Added small DCDC alternative for LED drive source; added current probe jumper for 3V3
2016-09-13 Added some components to support cheap RTC chips other than DS1307+
2016-09-13 Modified SolderJumper footprint to more distinguish look
2016-09-14 Added an alternative USB-to-serial brigde CP2104 (which is easily obtained from reliable distributors)
2016-09-15 Modified diode footprint cathode mark finer, and more
2016-09-16 Trace fix. I did it all for the impedance.
2016-09-18 Trace fix. This will be very close to final board design before garber-out.
2016-09-19 Trace fix. This will be final board design before garber-out.
2016-09-29 Final prototype rev.1
2016-10-04 Added nodemcu style reset circuit
2016-10-04 Modified directory structure
2016-10-10 Added initial firmware tree; It can display gradation on the LED
2016-10-13 Using interrupt to make fdisplay less flicker; unstable
2016-10-17 Changed pin assign to use hardware SPI
2016-10-19 Added hardware SPI support code (works)
2016-10-20 Introduced spread spectrum clock
2016-10-21 Various improvements, added a phase to reconfigure LED1642
2016-10-22 Added a demo code
2016-10-25 Added IR control support, button sens support
2016-10-27 Get IR controller work; added font directory
2016-11-01 Added a test code for BME280
2016-11-01 Schematic sheet rearrangement
2016-11-04 Rename; Large preparation for 64x48 dot matrix clock
2016-11-04 Added ADC (ambient brigheness) test
2016-11-05 Arranged large part: dot matrix.
2016-11-10 Done connecting LED driver
2016-11-10 Done overall component arrangement
2016-11-14 Done rough layout
2016-11-15 Silk fix; Various fixes
2016-11-15 Added led alignment ruler
2016-11-15 DRC clean
2016-11-16 fixed holes under pad
2016-11-16 pattern fix
2016-11-17 Bypass capacitor improvements, various adjustments
2016-11-18 Various improvements
2016-11-19 Modified some components' foot print
2016-11-20 DRC complete
2016-11-21 Changed USB-UART chip from CH340G to CP2104
2016-11-22 Added some status LEDs; Various improvements
2016-11-23 Rearrange buttons and more
2016-11-23 DRC clear
2016-11-25 Noise handling improved
2016-11-26 Modified USB connector footprints and more
2016-11-27 Silk adjustment and more
2016-11-27 Fogot saving
2016-11-28 Added copper pour on the matrix area
2016-11-29 Improved noise handling
2016-11-30 Make PCB corner round; Arranged DC input network
2016-11-30 Impedance improvements
2016-11-30 DRC fix
2016-12-01 Fixed noisy signal path
2016-12-02 Fixed tact-sw footprint; Removed PCB area under anttena
2016-12-03 Relocated traces of noise sensitive
2016-12-03 Fixed resistor position
2016-12-06 copper area fix
2016-12-08 To be able to disconnect noisy RXD line
2016-12-08 Improved bypass cap
2016-12-10 Improved LED drive current filter
2016-12-12 Made USB-UART bridge dettachable
2016-12-13 To be able to get diagnostic result from LED driver
2016-12-14 Small fixes; should be very close to final design of rev.2
2016-12-15 Added dee-ko-chan silk art
2016-12-16 Gerber-out, revision 2
2016-12-19 Commit toward rev2.1. loosen slot width to compat with other PCB manufacturres
2016-12-21 Improved ESD handling
2016-12-28 Component size and position improvements
2017-02-07 Varous improvements including adjusting SOIC pad width, increasing CP2104 bypass cap ... etc
2017-02-18 Update to newest kicad's library; Fixing USB-to-serial drive strength problems (Silks and pattern tuning not yet done)
2017-02-19 Adjusted area spaces
2017-03-01 Weak signal separation
2017-03-09 First commit for 64x48 dotmatrix drive; works
2017-03-16 Re-layout LED drivers to reduce EMI
2017-03-20 Layout adjustments toward proto rev.3
2017-03-23 Added long transmission line terminator; DRC clear
2017-03-25 Layout improvements; DRC clear
2017-03-28 Layout adjustment; I did it all for the impedance
2017-03-28 Added more guard traces; DRC may not clear
2017-03-31 Improved weak signal guards; Added WROOM-02 socket pattern; Improved USB-UART power filtering
2017-04-01 Layout improvements; Should be close to Gerber out
2017-04-04 Separated GND and GNDPWR; Filled matrix with copper; DRC clear (2 errors expected)
2017-04-09 Various adjustments; Very very close to Prototype Rev.3 Gerber out
2017-04-09 Some improvements; Still close to the Gerber out
2017-04-10 Added a logo
2017-04-11 Gerber out, prototype rev.3
2017-05-11 Added font drawing framework, and takao-P based bitmap font
2017-06-14 Updated .gitignore
2017-06-14 Firmware improved; mainly for font handling
2017-06-14 Hardware design update toward final release
2017-06-24 Added bitmap on-rom font support and more
2017-06-24 Fixed ambient light sensor voltage range; and more
2017-06-24 Added comments and fixed DRC
2017-06-26 Modified USBGND->GND; Layout improvement for edge skrew hole
2017-06-27 Paranoia fix
2017-06-27 To ignore OpenOffice lock file
2017-06-28 Wrote initial UI framework and LED check UI
2017-06-28 Incomplete settings manager added
2017-06-28 Improved grounding
2017-06-28 Check overlap of pads and holes; DRC clear
2017-06-29 To use another SPIFFS for storing setting data
2017-06-29 Compreted cross-GND vias
2017-06-30 GND pattern improved; Should be just before gerber out
2017-07-05 PCB production rev.1
2017-07-05 On the way to make OTA cable of one combined archive binary file
2017-07-05 Finished combined firmware OTA; UI thread dead ... now working hard on
2017-07-06 UI framework renewed; No more using coroutine; LED PWM clock now stops during OTA
2017-07-10 Experimental EMI reduction by changing LED PWM clock
2017-07-12 Fixed font drawing out-of-screen behaviour; Adding string edit ui; Implemented automatic EMI reduction according with WiFi channel
2017-07-22 To use push-terminal-block for IR LED; About to use diferrencial clocking for LED PWM clock to reduce EMI
2017-07-22 Added some igonoring file
2017-07-22 Modified e and g glyph; added small chars for IP addresses
2017-07-22 Varous improvements; I should make commit more frequently though.
2017-07-22 Added files for web interface
2017-07-25 I'm sorry to say that I didn't make each commit meaningful ... I'm lazy to commit because It's early stage of development ... yes it's a kind of sabotage...
2017-07-28 Various improvements; Again, I'm too lazy to keep track of my change.
2017-08-01 compressed js files
2017-08-01 Added some glyphs
2017-08-01 Fixed seeking problem
2017-08-01 fixed settings import problem
2017-08-01 Implemented NTP server settings store/load
2017-08-01 Some fixes
2017-08-01 Fixed interrupt overrun problem; Added initial clock main screen
2017-08-03 Added sensors source module; Added 4x5 small font; Made main clock UI (sensor display and scroll text not yet)
2017-08-07 Set theme jekyll-theme-minimal
2017-08-08 Various improvements; sorry for the big commit
2017-08-16 Added C92 version of How-to make document
2017-09-01 Added .gitignore
2017-09-01 Schematic structure rearranged
2017-11-16 Added schematic pdf
